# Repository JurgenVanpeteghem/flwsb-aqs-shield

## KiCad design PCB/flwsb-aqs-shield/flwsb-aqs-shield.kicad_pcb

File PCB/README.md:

# Air quality sensor shield

# PCB
For the project we made a seperate sensorboard wich contains all the sensors we use for the projetc. The purpose of this connector board is to connect all sensors to the main FLWSB. The FLWSB can collect the data drom the sensors on this board and send this data over lorawan.

The board contains following sensors to measure differnent parameters of airquality: 
  - BME280 (relative humidity- and tamperature 3,3V - I2C)
  - SGP41 (VOC en NOx sensor 3,3V - I2C)
  - SCD41 (CO2 sensor 3,3V - I2C)
  - Jst-connector for SPS30 (particulate matter sensor 5V - I2C)

additionally some pinheaders where added to connect a GY-NEO6MV2 GPS module and a solar power manager board to provide solar power to the board.

To solder the SMD sensors to the board solder paste was applied to the pads on the PCB. Then we soldered the sensors with a reflow oven. To get the sensors to work, we had to put some boards a second time in the reflow oven.

# Bill of materials
| Component  | amount  |
|---|---|
| 15 pin header female | 2 |
| 4 pin header male | 2 |
| SPS30 JST 5 pin connector | 1 |
| SDC41 | 1 |
| SGP41 | 1 |
| BME280 | 1 |
| capacitor 1µF  | 2  |
| capacitor 100nF  | 4  |
| resistor 4,7Ω  | 1  |

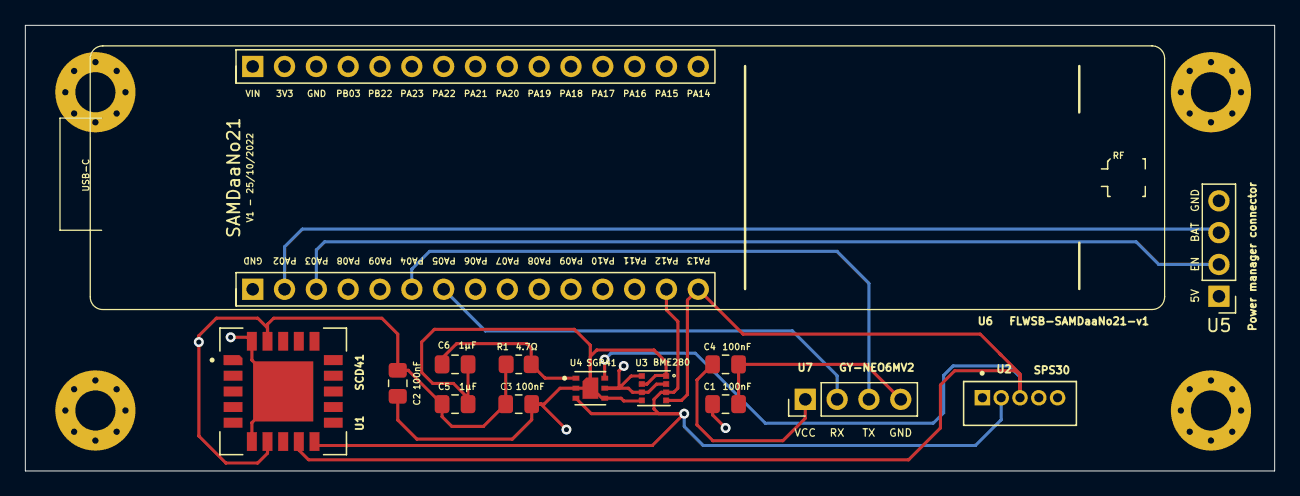
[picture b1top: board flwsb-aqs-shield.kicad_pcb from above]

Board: 4 copper layers, 99.7 x 35.6 mm, 18 parts (0 on the bottom side), 10 nets.

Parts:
C1, C2, C3, C4: 100nF; C_0805_2012Metric_Pad1.18x1.45mm_HandSolder
C5, C6: 1µF; C_0805_2012Metric_Pad1.18x1.45mm_HandSolder
H1, H2, H3, H4: MountingHole_Pad; MountingHole_3.2mm_M3_Pad_Via
R1: 4.7Ω; R_0805_2012Metric_Pad1.20x1.40mm_HandSolder
U1: SCD41
U2: SPS30; JST_B5B-ZR(LF)(SN)
U3: BME280
U4: SGP41
U5: Power manager connector; PinHeader_1x04_P2.54mm_Vertical
U6: FLWSB-SAMDaaNo21-v1
U7: GY-NEO6MV2; PinHeader_1x04_P2.54mm_Vertical

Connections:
+3V3: C2.1, C3.1, C4.2, C5.1, R1.1, U1.7 (VDD), U1.19 (VDDH), U3.2 (CSB), U3.6 (VDDIO), U3.8 (VDD), U4.5 (VDDH), U6.29 (3V3), U7.1 (VCC)
+5V: C1.1, U2.1 (VDD), U5.1 (5V), U6.30 (VIN)
BAT: U5.3 (ON/OFF_BAT), U6.2 (PA02)
EN: U5.2 (ON/OFF_EN), U6.3 (PA03)
GND: C1.2, C2.2, C3.2, C4.1, C5.2, C6.2, H1.1, H2.1, H3.1, H4.1, U1.6 (GND), U1.20 (GND), U1.21 (GND), U2.4 (SEL), U2.5 (GND), U3.1 (GND), U3.5 (SDO), U3.7 (GND), U4.2 (VSS), U4.4 (N/A), U4.7 (EXP), U5.4 (GND), U6.1 (GND), U6.28 (GND), U7.4 (GND)
unnamed: C6.1, R1.2, U4.1 (VDD)
S0RX: U6.6 (PA04), U7.3 (TX)
S0TX: U6.7 (PA05), U7.2 (RX)
SCL: U1.9 (SCL), U2.3 (SCL), U3.4 (SCK), U4.6 (SCL), U6.15 (PA13)
SDA: U1.10 (SDA), U2.2 (SDA), U3.3 (SDI), U4.3 (SDA), U6.14 (PA12)
